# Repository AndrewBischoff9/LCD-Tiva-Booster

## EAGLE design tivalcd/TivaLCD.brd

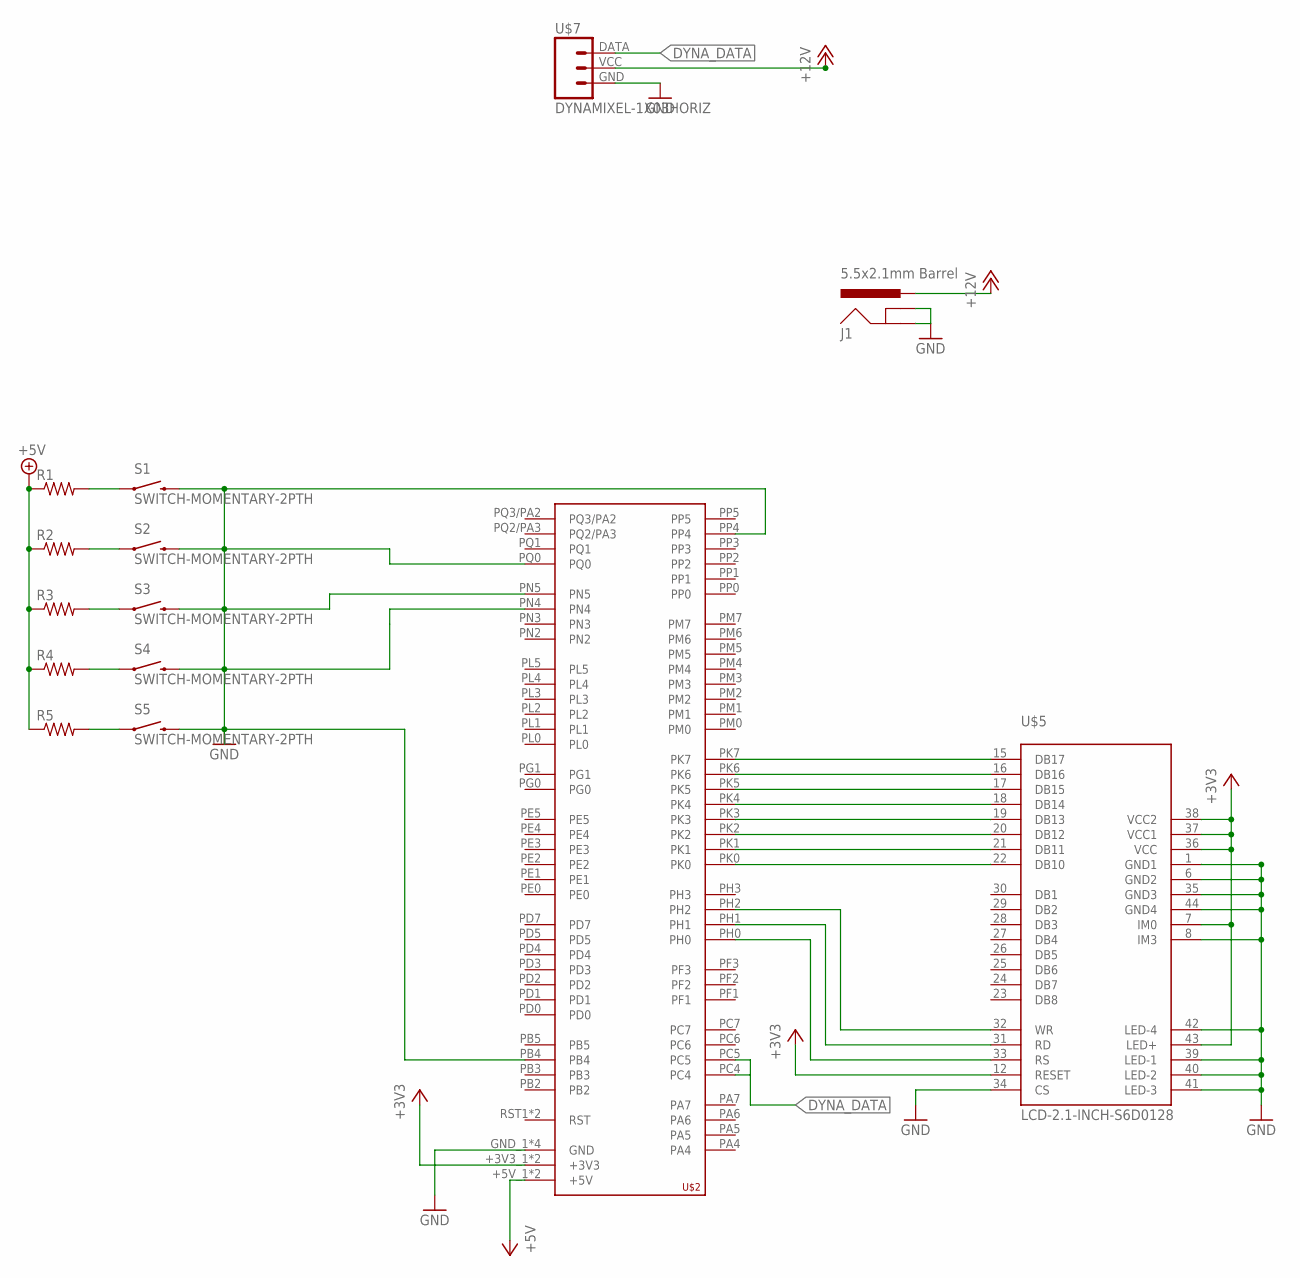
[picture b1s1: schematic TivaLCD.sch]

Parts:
J1: 5.5x2.1mm Barrel; POWER_JACK_SMD
R1, R2, R3, R4, R5: RESISTOR1206; 1206
S1, S2, S3, S4, S5: SWITCH-MOMENTARY-2PTH; TACTILE-PTH
U$2: TIVA-C-CONNECTED
U$5: LCD-2.1-INCH-S6D0128; LCD-2.1-44PIN-0.8
U$7: DYNAMIXEL-1X03HORIZ; MLX-SPOX5268-3PIN

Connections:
+3V3: U$2.+3V3_1 (+3V3), U$2.+3V3_2 (+3V3), U$5.7 (IM0), U$5.12 (RESET), U$5.36 (VCC), U$5.37 (VCC1), U$5.38 (VCC2), U$5.43 (LED+)
+5V: R1.1, R2.1, R3.1, R4.1, R5.1, U$2.+5V_1 (+5V), U$2.+5V_2 (+5V)
+12V: J1.VIN0 (PWR), U$7.VCC
DYNA_DATA: U$2.PC4, U$2.PC5, U$7.DATA
GND: J1.GND (GNDBREAK), J1.P$4 (GND), S1.3 (2), S2.3 (2), S3.3 (2), S4.3 (2), S5.3 (2), U$2.GND_1 (GND), U$2.GND_2 (GND), U$2.GND_3 (GND), U$2.GND_4 (GND), U$2.PB4, U$2.PN5, U$2.PP4, U$2.PQ0, U$5.1 (GND1), U$5.6 (GND2), U$5.8 (IM3), U$5.34 (CS), U$5.35 (GND3), U$5.39 (LED-1), U$5.40 (LED-2), U$5.41 (LED-3), U$5.42 (LED-4), U$5.44 (GND4), U$7.GND
unnamed: U$2.PK0, U$5.22 (DB10)
unnamed: U$2.PK1, U$5.21 (DB11)
unnamed: U$2.PK2, U$5.20 (DB12)
unnamed: U$2.PK3, U$5.19 (DB13)
unnamed: U$2.PK4, U$5.18 (DB14)
unnamed: U$2.PK5, U$5.17 (DB15)
unnamed: U$2.PK6, U$5.16 (DB16)
unnamed: U$2.PK7, U$5.15 (DB17)
unnamed: U$2.PH0, U$5.33 (RS)
unnamed: U$2.PH1, U$5.31 (RD)
unnamed: U$2.PH2, U$5.32 (WR)
unnamed: R1.2, S1.1
unnamed: R2.2, S2.1
unnamed: R3.2, S3.1
unnamed: R4.2, S4.1
unnamed: R5.2, S5.1

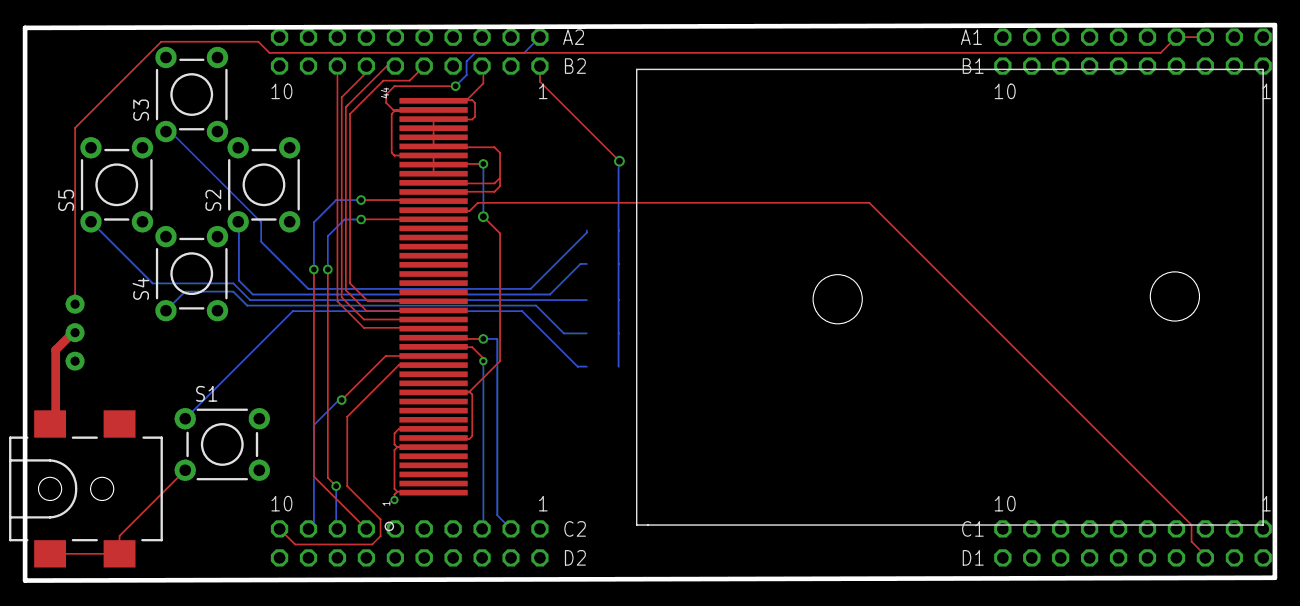
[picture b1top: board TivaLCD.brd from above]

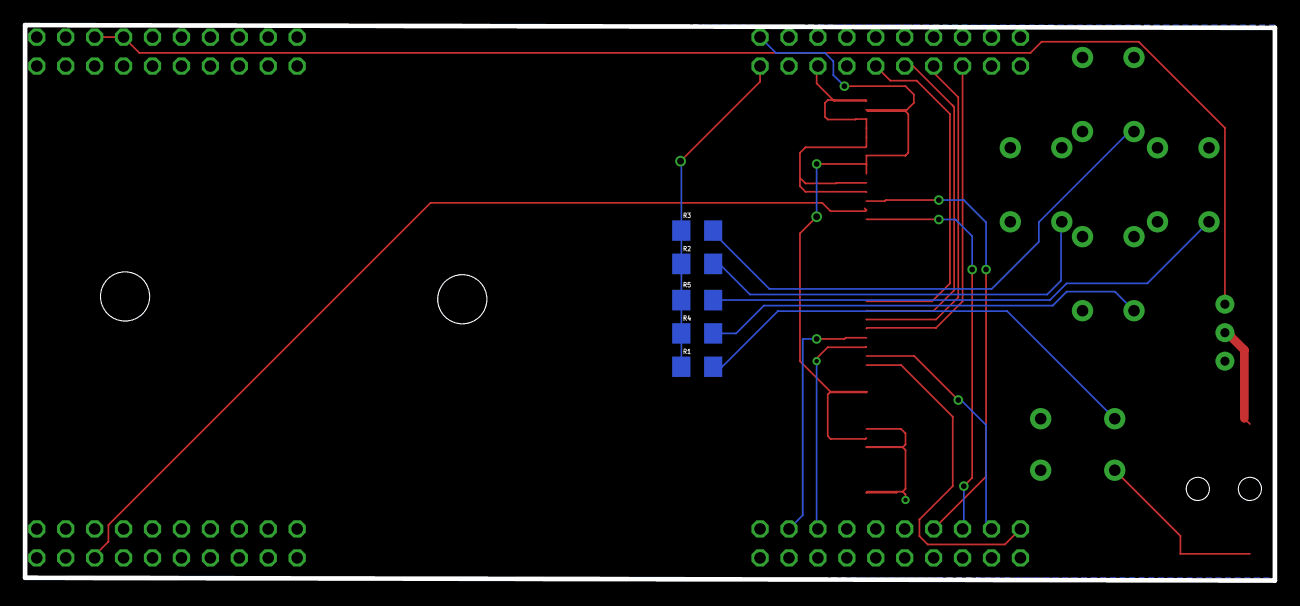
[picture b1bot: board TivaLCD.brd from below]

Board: 2 copper layers, 109.7 x 48.8 mm, 16 parts (5 on the bottom side), 21 nets.

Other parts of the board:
U$3, U$4: #8_SCREW

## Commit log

2016-02-20 :octocat: Added .gitattributes & .gitignore files
2016-04-22 Updated routing

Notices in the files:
parts and their libraries:
SparkFun-Electromechanical: Licensing: Creative Commons ShareAlike 4.0 International - https://creativecommons.org/licenses/by-sa/4.0
